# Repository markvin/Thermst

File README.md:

# Thermst

A hardware and software complex for controlling a heating element operating from a 230 V AC network.

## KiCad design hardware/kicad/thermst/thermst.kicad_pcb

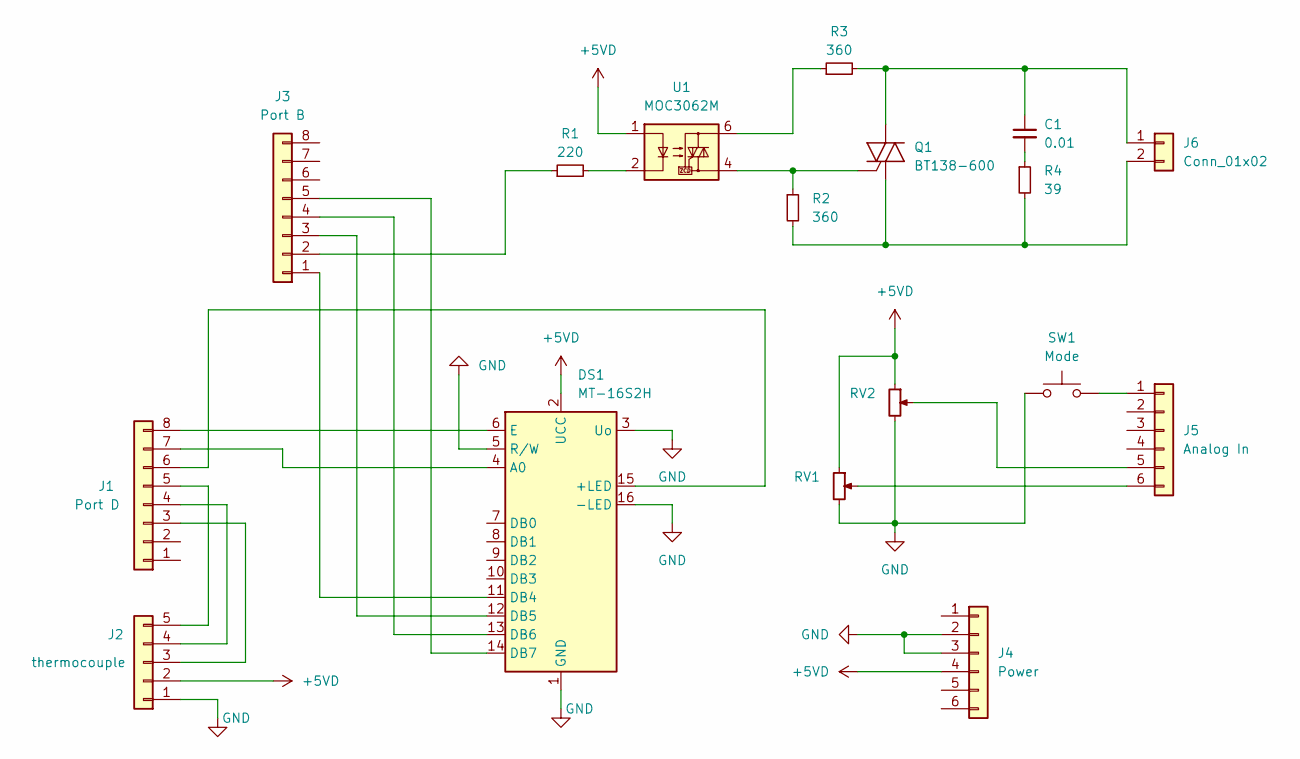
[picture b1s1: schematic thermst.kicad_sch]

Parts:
C1: 0.01; C_Rect_L13.0mm_W4.0mm_P10.00mm_FKS3_FKP3_MKS4
DS1: MT-16S2H; MT16S2H
J1: Port D; PinHeader_1x08_P2.54mm_Vertical
J2: thermocouple; PinHeader_1x05_P2.54mm_Horizontal
J3: Port B; PinHeader_1x08_P2.54mm_Vertical
J4: Power; PinHeader_1x06_P2.54mm_Vertical
J5: Analog In; PinHeader_1x06_P2.54mm_Vertical
J6: Conn_01x02; SolderWire-0.75sqmm_1x02_P4.8mm_D1.25mm_OD2.3mm
Q1: BT138-600; TO-220-3_Vertical
R1: 220; R_Axial_DIN0309_L9.0mm_D3.2mm_P12.70mm_Horizontal
R2, R3: 360; R_Axial_DIN0414_L11.9mm_D4.5mm_P15.24mm_Horizontal
R4: 39; R_Axial_DIN0414_L11.9mm_D4.5mm_P15.24mm_Horizontal
RV1: Temperature; Potentiometer_ACP_CA9-V10_Vertical
RV2: Power; Potentiometer_ACP_CA9-V10_Vertical
SW1: Mode; SW_PUSH_6mm_H13mm
U1: MOC3062M; DIP-6_W7.62mm

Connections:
+5VD: DS1.2 (UCC), J2.2, J4.4, RV1.1, RV2.1, U1.1
GND: DS1.1 (GND), DS1.3 (Uo), DS1.5 (R/W), DS1.16 (-LED), J2.1, J4.2, J4.3, RV1.3, RV2.3, SW1.1
unnamed: C1.2, R4.1
unnamed: DS1.15 (+LED), J1.6
unnamed: DS1.4 (A0), J1.7
unnamed: DS1.11 (DB4), J3.1
unnamed: DS1.12 (DB5), J3.3
unnamed: DS1.13 (DB6), J3.4
unnamed: DS1.14 (DB7), J3.5
unnamed: DS1.6 (E), J1.8
unnamed: J1.3, J2.3
unnamed: J1.4, J2.4
unnamed: J1.5, J2.5
unnamed: J3.2, R1.1
unnamed: J5.1, SW1.2
unnamed: J5.5, RV2.2
unnamed: J5.6, RV1.2
unnamed: C1.1, J6.1, Q1.2 (A2), R3.2
unnamed: J6.2, Q1.1 (A1), R2.2, R4.2
unnamed: Q1.3 (G), R2.1, U1.4
unnamed: R1.2, U1.2
unnamed: R3.1, U1.6

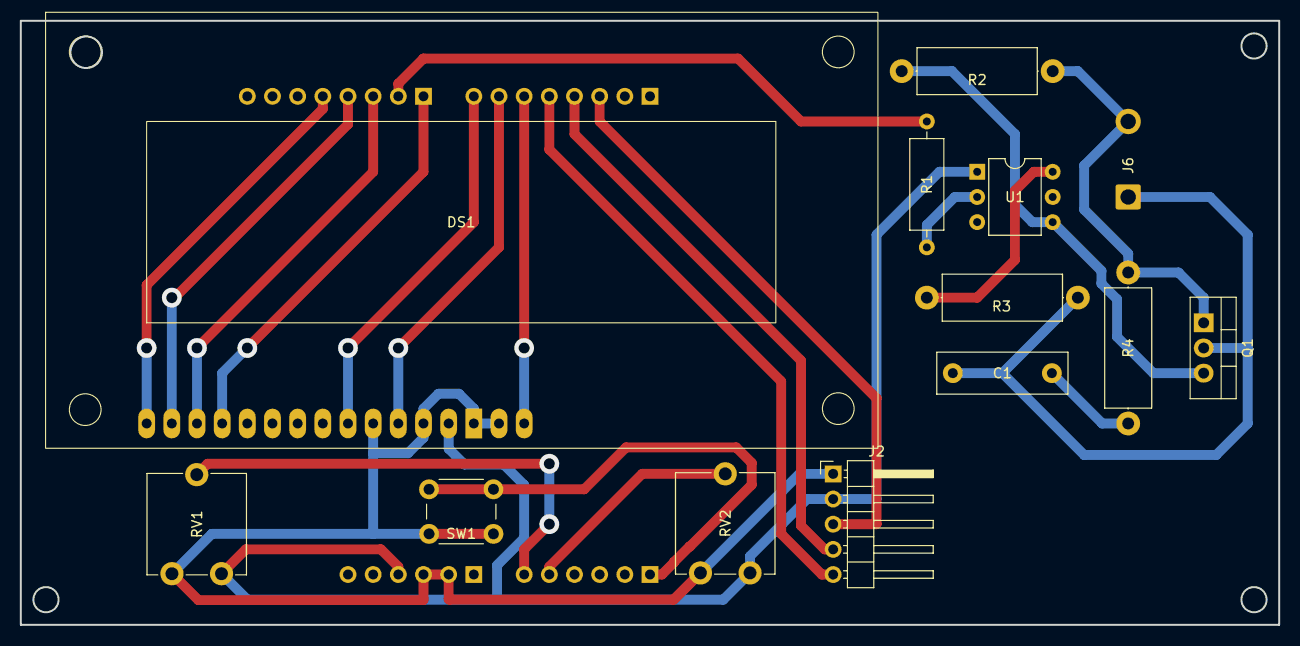
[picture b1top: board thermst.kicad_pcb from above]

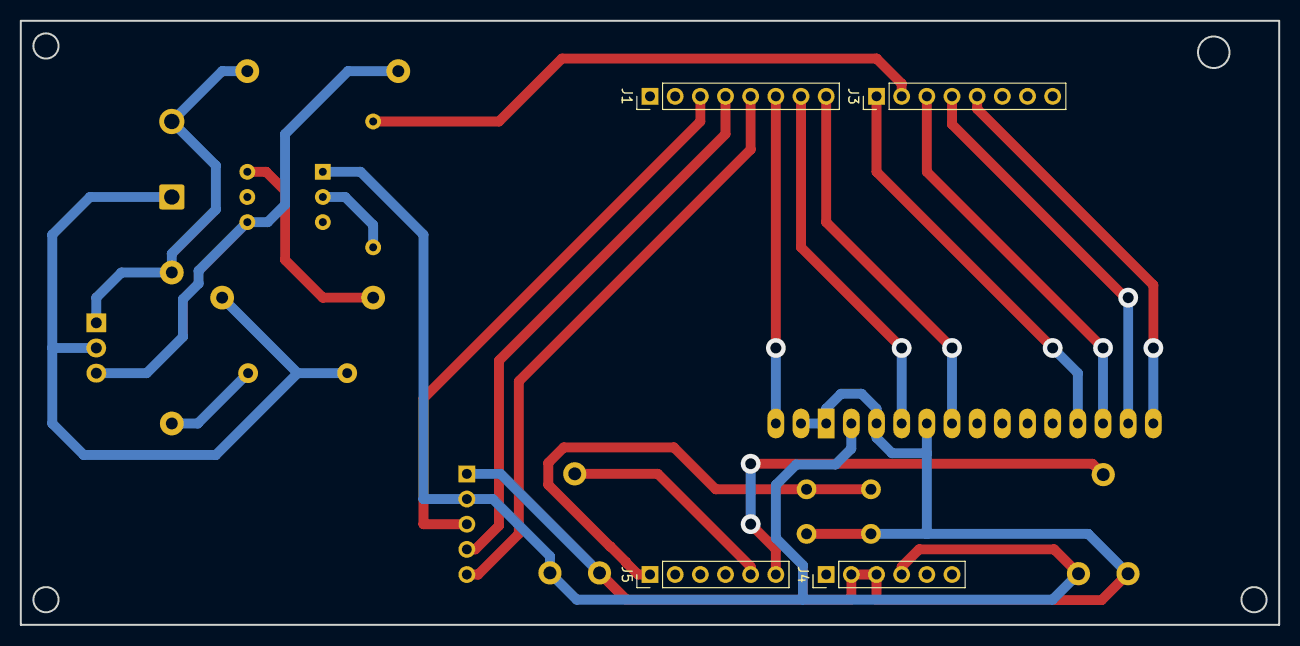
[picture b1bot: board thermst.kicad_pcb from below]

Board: 2 copper layers, 127.0 x 61.0 mm, 17 parts (4 on the bottom side), 22 nets.

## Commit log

2023-11-01 Add EEPROM storage functions
2023-11-03 Add hardware (kicad) content
2023-11-10 Fix bugs after hardware assembled
2023-11-10 Add max6675 datasheet
2023-11-12 Remove kicad backups
2023-12-16 Change power display scenario in auto mode
2023-12-17 Remove unnecessary dependencies from platform.ini
